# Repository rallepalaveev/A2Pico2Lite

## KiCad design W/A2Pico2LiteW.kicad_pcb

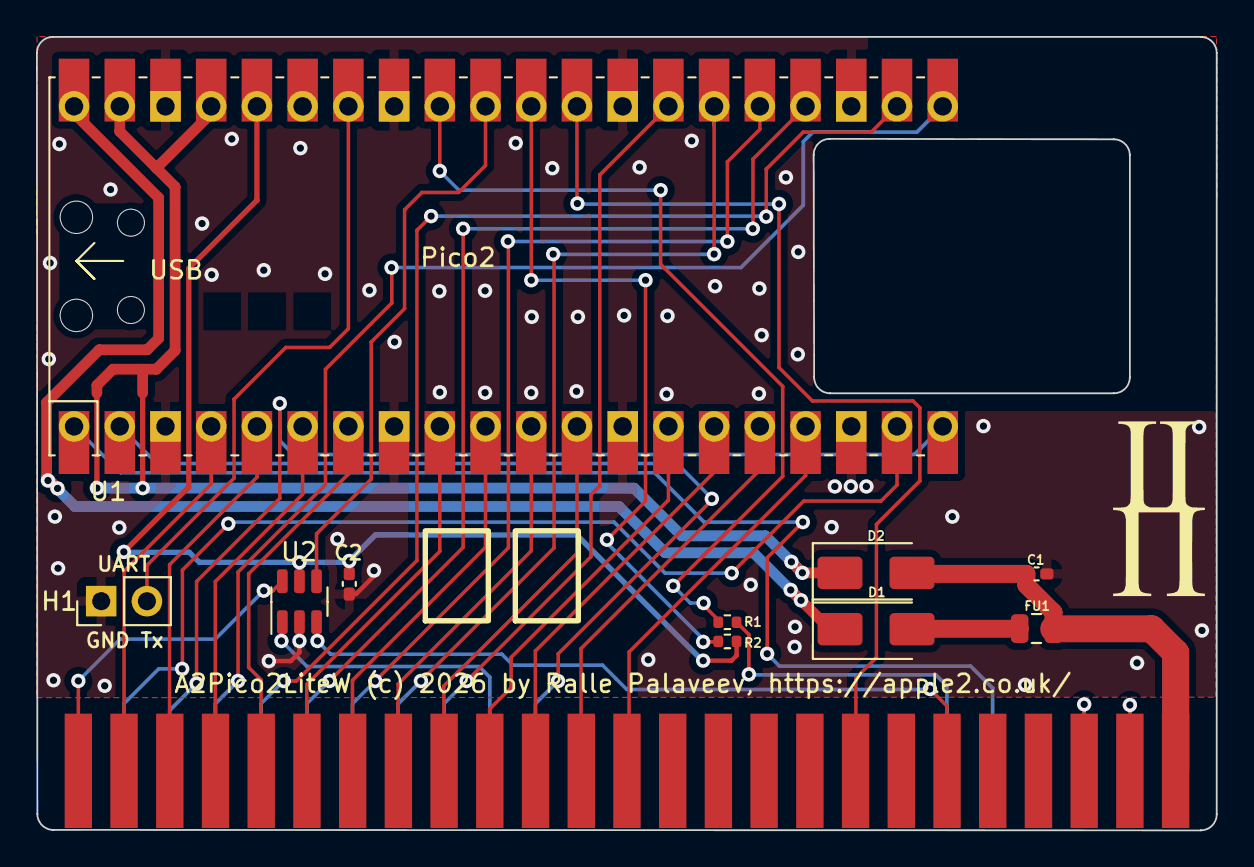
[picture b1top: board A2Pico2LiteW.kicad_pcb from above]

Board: 2 copper layers, 65.5 x 44.1 mm, 10 parts (0 on the bottom side), 10 nets.

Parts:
C1, C2: 100n; C_0402_1005Metric_Pad0.74x0.62mm_HandSolder
D1, D2: SS14; D_SMA
FU1: 500mA; Fuse_0805_2012Metric
H1: PinHeader_1x02_P2.54mm_Vertical
R1, R2: 1k; R_0402_1005Metric
U1: Pico; RPi_PicoW_SMD_TH
U2: SN74LVC1G11DBVR; SOT-23-6

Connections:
3.3V: C2.1, R2.1, U1.36 (3V3), U2.5
5V: C1.1, D2.2, FU1.1
5V-1: D1.2, FU1.2
GND: C1.2, C2.2, H1.1, U1.3 (GND), U1.8 (GND), U1.13 (GND), U1.18 (GND), U1.23 (GND), U1.28 (GND), U1.33 (AGND), U1.38 (GND), U2.2
RUN: R2.2, U1.30 (RUN)
Tx: H1.2, U1.34 (GPIO28_ADC2)
VBUS: D1.1, U1.40 (VBUS)
VSYS: D2.1, U1.37 (3V3_EN), U1.39 (VSYS)
~Enable: U1.31 (GPIO26_ADC0), U2.4
~Reset_: R1.2, U1.32 (GPIO27_ADC1)

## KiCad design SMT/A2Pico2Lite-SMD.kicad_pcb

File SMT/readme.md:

# A2Pico2 Reference Hardware

This repository is the home of the A2Pico2Lite-SMD reference hardware based on the RP2354A processor. It is an expansion mass storage card for Apple2 computers. It is a limited version of the A2Pico2 design with the restriction that it can use only a USB stick as a storage device. Please refer to the repository at https://github.com/oliverschmidt/a2pico for general information on A2Pico2.

## Hardware Revision History

Version 1.0 is the initial design.

Version 1.1 is the current version with added parallel capacitors to the voltage dividers of the 5V non-tolerant GPIOs for correction of the waveforms.

The GPIO usage is as follows:

| GPIO    | Usage     |
|:--------|:----------|
| 0       |  IRQ      |
| 1       |  PHI0     |
| 2 - 13  | A0 - A11  |
| 14-21   | D0-D7     |
| 25      | LED       |
| 26      | DEVSEL    |
| 27      | IOSEL     |
| 28      | IOSTB     |

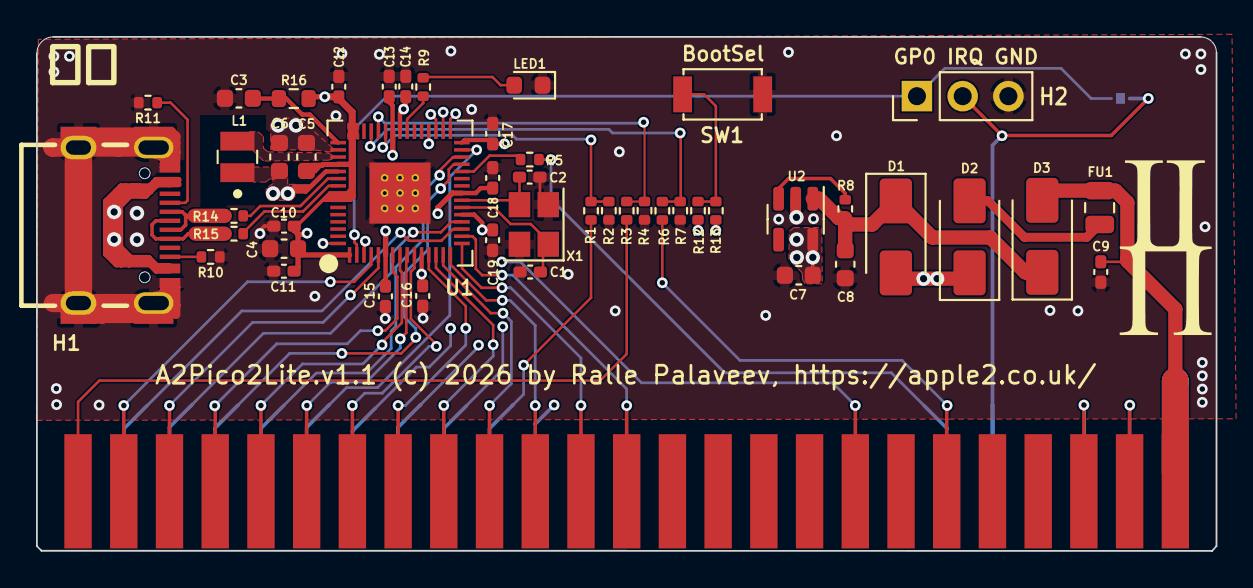
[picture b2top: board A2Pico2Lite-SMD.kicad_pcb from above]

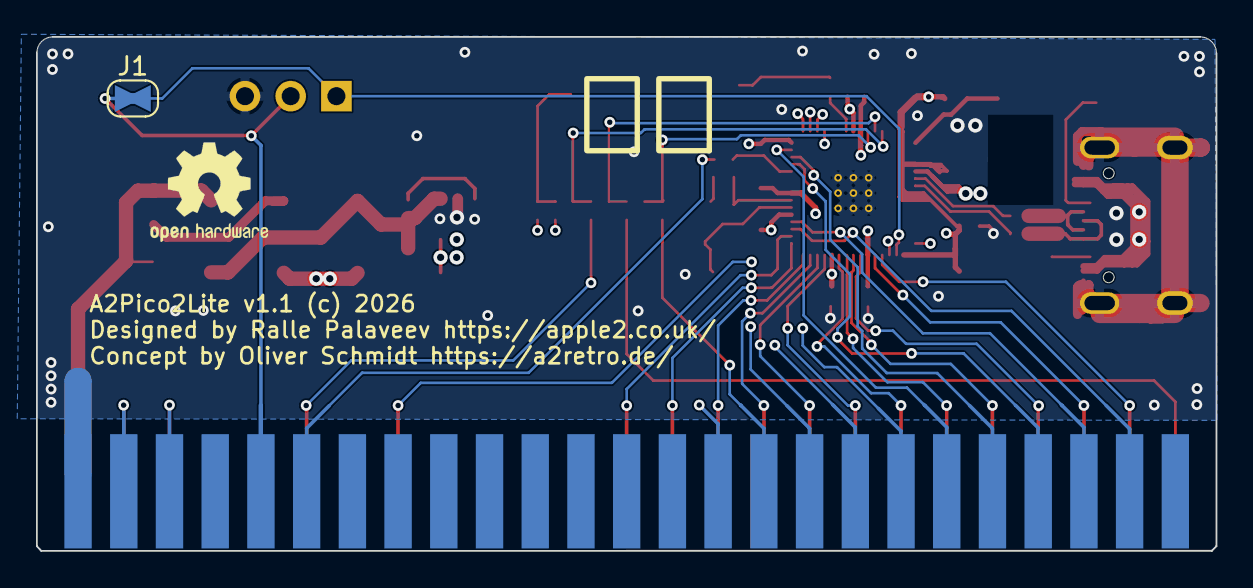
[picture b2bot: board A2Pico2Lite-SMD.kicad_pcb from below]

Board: 4 copper layers, 65.5 x 28.6 mm, 50 parts (2 on the bottom side), 28 nets.

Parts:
C1, C2: 12pF; C_0402_1005Metric_Pad0.74x0.62mm_HandSolder
C3, C4, C5: 4.7uF; C_0603_1608Metric
C6, C7, C8: 10uF; C_0603_1608Metric
C9, C10, C11, C12, C13, C14, C15, C16, C17, C18, C19: 100n; C_0402_1005Metric_Pad0.74x0.62mm_HandSolder
D1, D2, D3: SS14; D_SMA
FU1: 500mA; Fuse_0805_2012Metric
G1: LOGO
G2: OSHW-Logo2_7.3x6mm_SilkScreen
H1: USB-C-16P-F(A40-00119-A52-12); USB2.0_TYPE-C(A40-00119-A52-12)
H2: PinHeader_1x03_P2.54mm_Vertical
J1: SolderJumper-2_P1.3mm_Bridged_RoundedPad1.0x1.5mm
L1: 3.3uH; L_Wuerth_MAPI-2512
LED1: LED_CHR; LED_0603_1608Metric
R1, R3, R6, R8, R9, R13: 1k; R_0402_1005Metric
R2, R4, R5, R7: 2k; R_0402_1005Metric
R10, R11: 5k1; R_0402_1005Metric
R12: 100k; R_0402_1005Metric
R14, R15: 27; R_0402_1005Metric
R16: 27; R_0603_1608Metric
SW1: SW_BOOTSEL; SW_SPST_B3U-1000P
U1: RP2354A_QFN-60_EP_7.75x7.75_Pitch0.4mm; RP2350A_QFN-60_EP_7.75x7.75_Pitch0.4mm
U2: ME6211; SOT-23-5
X1: Crystal_SMD_Abracon_ABM8AIG-4Pin_3.2x2.5mm

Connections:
+1.1V: C6.1, C13.1, C15.1, C18.1, L1.1, U1.6, U1.23, U1.39, U1.50
+1.1V_reg: L1.2, U1.48
+3V3: C4.1, C5.1, C7.2, C10.1, C11.1, C12.1, C14.1, C16.1, C17.1, C19.1, R12.1, R16.2, U1.1, U1.11, U1.20, U1.30, U1.38, U1.44, U1.45, U1.49, U1.53, U1.54, U2.5 (VOUT)
+5V: C9.1, D3.2, FU1.1
+5V-1: D2.2, FU1.2
/D+: R15.2, U1.52
/D-: R14.2, U1.51
/LDO_EN: R8.1, U2.3 (EN)
/USB_D+: H1.A6, H1.B6, R15.1
/USB_D-: H1.A7, H1.B7, R14.1
/VIN: C8.1, D1.1, D3.1, R8.2, U2.1 (VIN)
BootSel: R12.2, R13.2, SW1.1 (A)
GND: C1.2, C2.2, C3.1, C4.2, C5.2, C6.2, C7.1, C8.2, C9.2, C10.2, C11.2, C12.2, C13.2, C14.2, C15.2, C16.2, C17.2, C18.2, C19.2, H1.0, H1.A1, H1.A12, H1.B1, H1.B12, H2.3, LED1.1 (K), R2.2, R4.2, R7.2, R10.2, R11.1, SW1.2 (B), U1.47, U1.61, U2.2 (GND), X1.2, X1.4
GPIO0: H2.1, J1.2, U1.2
GPIO25: R9.2, U1.37
LED: LED1.2 (A), R9.1
QSPI_SS: R13.1, U1.60
REG_AVDD: C3.2, R16.1, U1.46
RUN: R5.1, U1.26
USB-A5: H1.A5, R11.2
USB-B5: H1.B5, R10.1
VBUS: D1.2, D2.1, H1.A4, H1.A9, H1.B4, H1.B9
XIN: C1.1, U1.21, X1.1
XOUT: C2.1, U1.22, X1.3
~DevSel_: R1.1, R2.1, U1.40
~IOSel_: R3.1, R4.1, U1.41
~IOStr_: R6.1, R7.1, U1.42
~IRQ: H2.2, J1.1

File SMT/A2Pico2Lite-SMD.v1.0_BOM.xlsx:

Comment | Designator | Footprint | JLCPCB Part #（optional）
18pF | C1,C2 | 0402 | C1549
6.3V 4.7uF 0603 | C3,C4,C5 | 0603 | C8032
6.3V 10uF 0603 | C6,C7,C8 | 0603 | C19702
16V 100nF 0402 | C9,C10,C11,C12,C13,C14,C15,C16,C17,C18,C19 | 0402 | C1525
SS14 | D1,D2,D3 | SMA(DO-214AC) | C2480
6V 500mA Resettable Fuse | FU1 | 0805-50 | C269104
USB-C-16P-F | H1 | USB-c | C2765186
3.3uH | L1 |  | C48783272
White LED | LED1 | SMD,1.6x0.8mm | C397049
1k | R1,R3,R6,R8,R9,R13 | 0402 | C11702
2k | R2,R4,R5,R7 | 0402 | C4109
5k1 | R10,R11 | 0402 | C25905
27 | R14,R15 | 0402 | C25100
100k | R12 | 0402 | C25741
27 | R16 | 0603 | C25190
TS-3025-A-A-B | SW1 |  | C720477
RP2354A | U1 | QFN-60_EP | C41378174
ME6211 | U2 |  | C82942
12MHz | Y1 | SMD3225-4P | C403945

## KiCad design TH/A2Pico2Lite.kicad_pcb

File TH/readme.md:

# A2Pico2 Reference Hardware

This repository is the home of the A2Pico2Lite-TH reference hardware based on the RPi Pico2. It is an expansion mass storage card for Apple2 computers. It is a limited version of the A2Pico2 design with the restriction that it can use only a USB stick as a storage device. Please refer to the repository at https://github.com/oliverschmidt/a2pico for general information on A2Pico2.

## Hardware Revision History

Version 1.0.

The GPIO usage is as follows:

| GPIO    | Usage     |
|:--------|:----------|
| 0       |  IRQ      |
| 1       |  PHI0     |
| 2 - 13  | A0 - A11  |
| 14-21   | D0-D7     |
| 25      | LED       |
| 26      | DEVSEL    |
| 27      | IOSEL     |
| 28      | IOSTB     |

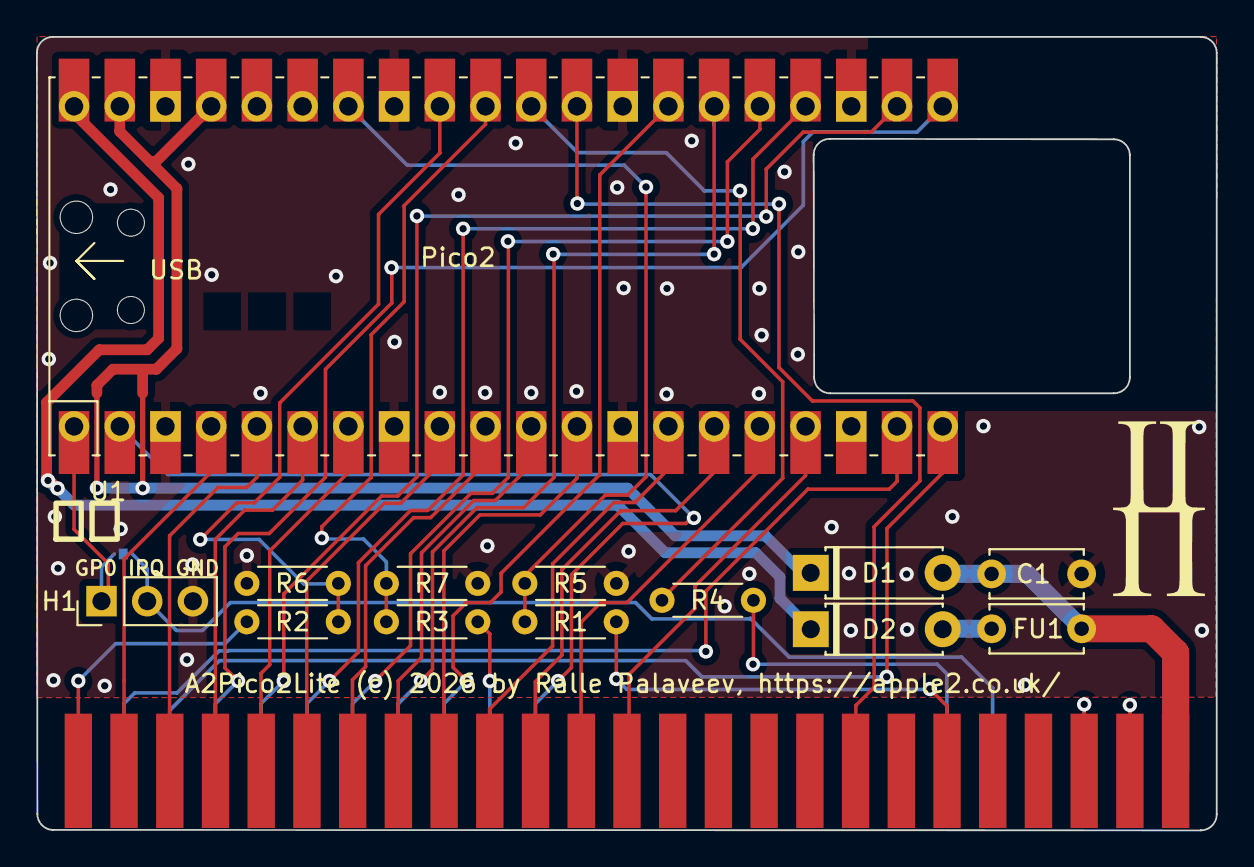
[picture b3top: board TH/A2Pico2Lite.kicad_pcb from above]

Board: 2 copper layers, 65.5 x 44.1 mm, 14 parts (1 on the bottom side), 11 nets.

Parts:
C1: 100n; C_Disc_D5.0mm_W2.5mm_P5.00mm
D1, D2: D_T-1_P5.08mm_Horizontal
FU1: 500mA; C_Disc_D5.0mm_W2.5mm_P5.00mm
H1: PinHeader_1x03_P2.54mm_Vertical
J2: SolderJumper-2_P1.3mm_Bridged_RoundedPad1.0x1.5mm
R1, R2, R3: 1k; R_Axial_DIN0204_L3.6mm_D1.6mm_P5.08mm_Horizontal
R4, R5, R6, R7: 2k; R_Axial_DIN0204_L3.6mm_D1.6mm_P5.08mm_Horizontal
U1: Pico; RPi_PicoW_SMD_TH

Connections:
5V: C1.1, D1.2, FU1.1
5V-1: D2.2, FU1.2
GND: C1.2, H1.3, R5.1, R6.2, R7.1, U1.3 (GND), U1.8 (GND), U1.13 (GND), U1.18 (GND), U1.23 (GND), U1.28 (GND), U1.33 (AGND), U1.38 (GND)
GPIO0: H1.1, J2.2, U1.1 (GPIO0)
RUN: R4.2, U1.30 (RUN)
VBUS: D2.1, U1.40 (VBUS)
VSYS: D1.1, U1.37 (3V3_EN), U1.39 (VSYS)
~DevSel_: R3.2, R7.2, U1.31 (GPIO26_ADC0)
~IOSel_: R2.1, R6.1, U1.32 (GPIO27_ADC1)
~IOStb_: R1.2, R5.2, U1.34 (GPIO28_ADC2)
~IRQ: H1.2, J2.1

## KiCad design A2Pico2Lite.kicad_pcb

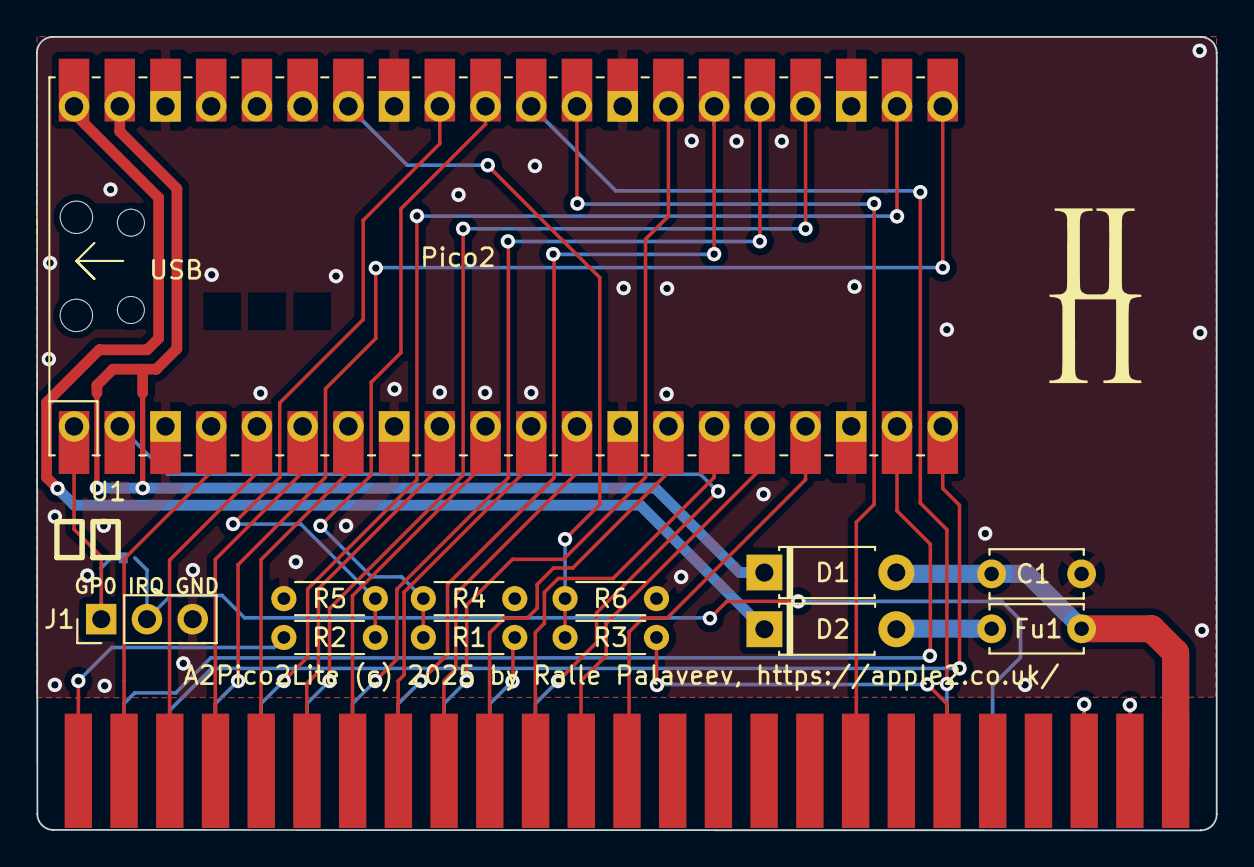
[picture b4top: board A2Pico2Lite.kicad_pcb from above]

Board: 2 copper layers, 65.5 x 44.1 mm, 13 parts (1 on the bottom side), 10 nets.

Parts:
C1: 100n; C_Disc_D5.0mm_W2.5mm_P5.00mm
D1, D2: D_T-1_P5.08mm_Horizontal
Fu1: 500mA; C_Disc_D5.0mm_W2.5mm_P5.00mm
J1: PinHeader_1x03_P2.54mm_Vertical
J2: SolderJumper-2_P1.3mm_Bridged_RoundedPad1.0x1.5mm
R1, R2, R3: 10k; R_Axial_DIN0204_L3.6mm_D1.6mm_P5.08mm_Horizontal
R4, R5, R6: 20k; R_Axial_DIN0204_L3.6mm_D1.6mm_P5.08mm_Horizontal
U1: Pico; RPi_PicoW_SMD_TH

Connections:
5V: C1.1, D1.2, Fu1.1
5V-1: D2.2, Fu1.2
GND: C1.2, J1.3, R4.1, R5.2, R6.1, U1.3 (GND), U1.8 (GND), U1.13 (GND), U1.18 (GND), U1.23 (GND), U1.28 (GND), U1.33 (AGND), U1.38 (GND)
GPIO0: J1.1, J2.2, U1.1 (GPIO0)
VBUS: D2.1, U1.40 (VBUS)
VSYS: D1.1, U1.39 (VSYS)
~DevSel_: R1.2, R4.2, U1.31 (GPIO26_ADC0)
~IOSel_: R2.1, R5.1, U1.32 (GPIO27_ADC1)
~IOStb_: R3.2, R6.2, U1.34 (GPIO28_ADC2)
~IRQ: J1.2, J2.1

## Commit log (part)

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2025-12-06 Rename A2Pico2Lite.pdf to TH/A2Pico2Lite.pdf
2025-12-06 Rename A2Pico2Lite.kicad_pro to TH/A2Pico2Lite.kicad_pro
2025-12-06 Rename A2Pico2Lite-SMD.pdf to SHD/A2Pico2Lite-SMD.pdf
2025-12-06 Rename A2Pico2Lite-SMD.pdf to A2Pico2Lite-SMD.pdf
2026-02-08 Update
    Added detailed information about A2Pico2 reference hardware, including hardware revision history and GPIO usage.
2026-02-08 Create readme.md for A2Pico2 reference hardware
    Added initial readme for A2Pico2 reference hardware with details on design and GPIO usage.
2026-02-08 Update repository name to A2Pico2Lite-SMT
2026-02-08 Fix typo in readme for A2Pico2Lite-SMD
2026-02-08 Fix typos in readme.md
2026-02-08 Fix typo in readme.md from 'innitial' to 'initial'
2026-04-21 Fix URL
2026-06-30 Add initial content to Readme.txt

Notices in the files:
A2Pico2Lite.kicad_pcb:
A2Pico2Lite (c) 2025
A2Pico2Lite (c) 2025 by Ralle Palaveev, https://apple2.co.uk
SMT/A2Pico2Lite-SMD.kicad_pcb:
A2Pico2Lite v1.1 (c) 2026
A2Pico2Lite.v1.1 (c) 2026 by Ralle Palaveev, https://apple2.co.uk
TH/A2Pico2Lite.kicad_pcb:
A2Pico2Lite (c) 2026
A2Pico2Lite (c) 2026 by Ralle Palaveev, https://apple2.co.uk
W/A2Pico2LiteW.kicad_pcb:
A2Pico2LiteW (c) 2026
A2Pico2LiteW (c) 2026 by Ralle Palaveev, https://apple2.co.uk
